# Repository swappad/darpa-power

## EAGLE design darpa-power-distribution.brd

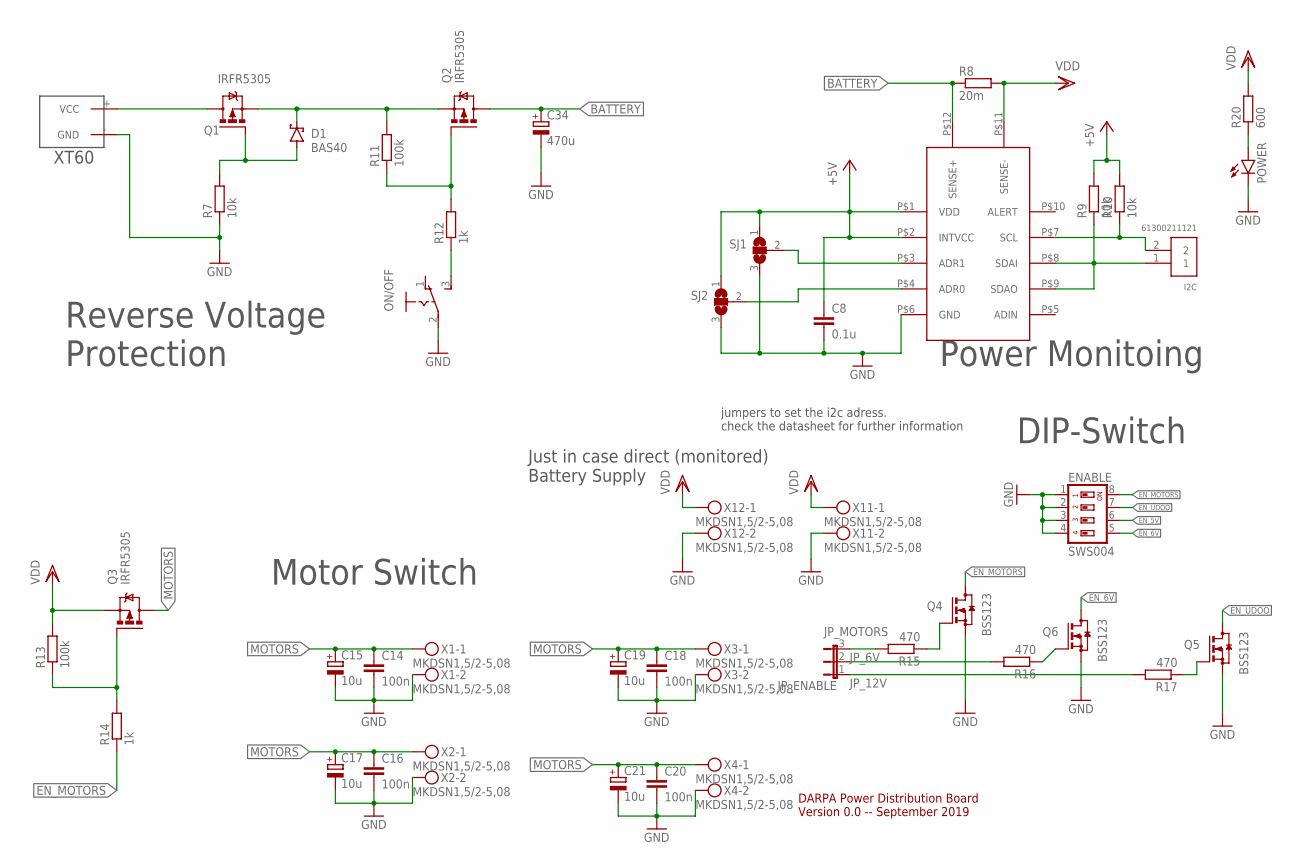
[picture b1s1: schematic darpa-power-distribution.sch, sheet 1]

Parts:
C8: 0.1u; C0805K
C14, C16, C18, C20: 100n; C0805K
C15, C17, C19, C21: 10u; E1,8-4
C34: 470u; E7,5-16
D1: BAS40; SOT23
ENABLE: SWS004; SMS-004
I2C: 61300211121
JP_ENABLE: JP2E; JP2
ON/OFF: M251
POWER: LEDSML0805; SML0805
Q1, Q2, Q3: IRFR5305; D-PAK_TO252AA
Q4, Q5, Q6: BSS123; SOT23
R7, R9, R10: 10k; R0805
R8: 20m; P0613/15
R11, R13: 100k; R0805
R12, R14: 1k; R0805
R15, R16, R17: 470; R0805
R20: 600; R0805
SJ1, SJ2: SJ2W; SJ_2
U$3: LTC2945
U$4: XT60
X1, X2, X3, X4, X11, X12: MKDSN1,5/2-5,08

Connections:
+5V: C8.1, R9.2, R10.2, SJ1.1, SJ2.1, U$3.P$1 (VDD), U$3.P$2 (INTVCC); also elsewhere on the board
BATTERY: C34.+, Q2.4 (D), R8.1, U$3.P$12 (SENSE+)
EN_5V: ENABLE.6; also elsewhere on the board
EN_6V: ENABLE.5, Q6.3 (D); also elsewhere on the board
EN_MOTORS: ENABLE.8, Q4.3 (D), R14.1
EN_UDOO: ENABLE.7, Q5.3 (D); also elsewhere on the board
GND: C8.2, C14.2, C15.-, C16.2, C17.-, C18.2, C19.-, C20.2, C21.-, C34.-, ENABLE.1, ENABLE.2, ENABLE.3, ENABLE.4, ON/OFF.2, POWER.C, Q4.2 (S), Q5.2 (S), Q6.2 (S), R7.1, SJ1.3, SJ2.3, U$3.P$6 (GND), U$4.- (GND), X1.2, X2.2, X3.2, X4.2, X11.2, X12.2; also elsewhere on the board
JP_6V: JP_ENABLE.2, R16.2
JP_12V: JP_ENABLE.1, R17.2
JP_MOTORS: JP_ENABLE.3, R15.2
MOTORS: C14.1, C15.+, C16.1, C17.+, C18.1, C19.+, C20.1, C21.+, Q3.4 (D), X1.1, X2.1, X3.1, X4.1
unnamed: D1.1 (A), Q1.1 (G), R7.2
unnamed: SJ1.2, U$3.P$3 (ADR1)
unnamed: SJ2.2, U$3.P$4 (ADR0)
unnamed: Q2.1 (G), R11.1, R12.2
unnamed: D1.3 (C), Q1.3 (S), Q2.3 (S), R11.2
unnamed: Q3.1 (G), R13.1, R14.2
unnamed: ON/OFF.3 (S), R12.1
unnamed: Q1.4 (D), U$4.+ (VCC)
unnamed: Q5.1 (G), R17.1
unnamed: Q4.1 (G), R15.1
unnamed: Q6.1 (G), R16.1
unnamed: POWER.A, R20.1
SCL: I2C.2, R10.1, U$3.P$7 (SCL)
SDA: I2C.1, R9.1, U$3.P$8 (SDAI), U$3.P$9 (SDAO)
VDD: Q3.3 (S), R8.2, R13.2, R20.2, U$3.P$11 (SENSE-), X11.1, X12.1; also elsewhere on the board

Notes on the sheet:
jumpers to set the i2c adress. check the datasheet for further information
Reverse Voltage Protection
Motor Switch
Power Monitoing
DIP-Switch
Just in case direct (monitored) Battery Supply
DARPA Power Distribution Board Version 0.0 -- September 2019

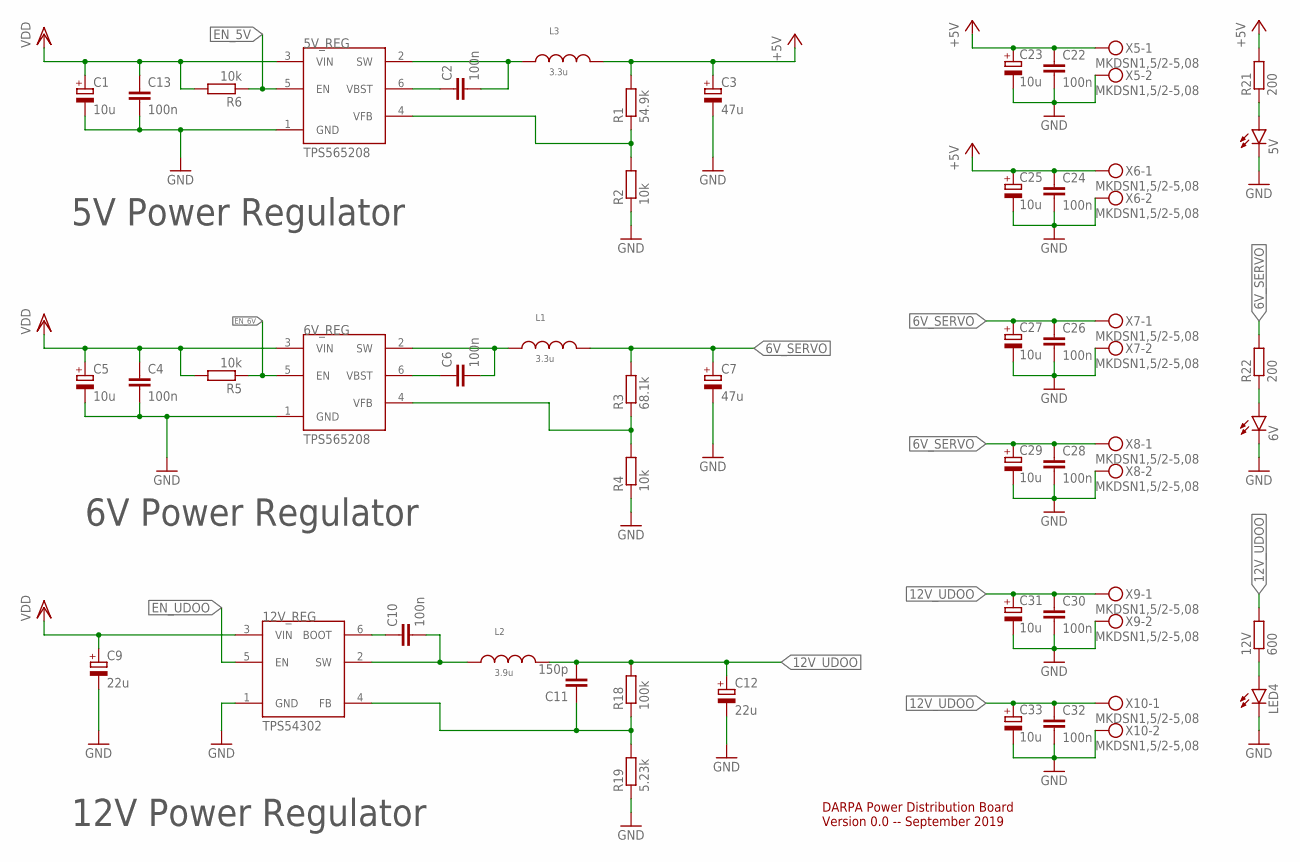
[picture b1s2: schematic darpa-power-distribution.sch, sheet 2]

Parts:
5V, 6V: LEDSML0805; SML0805
5V_REG, 6V_REG: TPS565208; SOT23-6
12V: 600; R0805
12V_REG: TPS54302; SOT23-6
C1, C5, C23, C25, C27, C29, C31, C33: 10u; E1,8-4
C2, C4, C6, C10, C13, C22, C24, C26, C28, C30, C32: 100n; C0805K
C3, C7: 47u; E2,5-6
C9, C12: 22u; E2,5-6
C11: 150p; C0805K
L1, L3: 3.3u; WE-CHSA_1011
L2: 3.9u; WE-CHSA_1011
LED4: LEDSML0805; SML0805
R1: 54.9k; R0805
R2, R4, R5, R6: 10k; R0805
R3: 68.1k; R0805
R18: 100k; R0805
R19: 5.23k; R0805
R21, R22: 200; R0805
X5, X6, X7, X8, X9, X10: MKDSN1,5/2-5,08

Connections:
6V_SERVO: C7.+, C26.1, C27.+, C28.1, C29.+, L1.2, R3.2, R22.2, X7.1, X8.1
12V_UDOO: 12V.2, C11.2, C12.+, C30.1, C31.+, C32.1, C33.+, L2.2, R18.2, X9.1, X10.1
+5V: C3.+, C22.1, C23.+, C24.1, C25.+, L3.2, R1.2, R21.2, X5.1, X6.1; also elsewhere on the board
EN_5V: 5V_REG.5 (EN), R6.1; also elsewhere on the board
EN_6V: 6V_REG.5 (EN), R5.1; also elsewhere on the board
EN_UDOO: 12V_REG.5 (EN); also elsewhere on the board
GND: 5V.C, 5V_REG.1 (GND), 6V.C, 6V_REG.1 (GND), 12V_REG.1 (GND), C1.-, C3.-, C4.2, C5.-, C7.-, C9.-, C12.-, C13.2, C22.2, C23.-, C24.2, C25.-, C26.2, C27.-, C28.2, C29.-, C30.2, C31.-, C32.2, C33.-, LED4.C, R2.1, R4.1, R19.1, X5.2, X6.2, X7.2, X8.2, X9.2, X10.2; also elsewhere on the board
unnamed: 5V_REG.4 (VFB), R1.1, R2.2
unnamed: 5V_REG.6 (VBST), C2.1
unnamed: 5V_REG.2 (SW), C2.2, L3.1
unnamed: 6V_REG.2 (SW), C6.2, L1.1
unnamed: 6V_REG.6 (VBST), C6.1
unnamed: 6V_REG.4 (VFB), R3.1, R4.2
unnamed: 12V_REG.6 (BOOT), C10.1
unnamed: 12V_REG.2 (SW), C10.2, L2.1
unnamed: 12V_REG.4 (FB), C11.1, R18.1, R19.2
unnamed: 5V.A, R21.1
unnamed: 6V.A, R22.1
unnamed: 12V.1, LED4.A
VDD: 5V_REG.3 (VIN), 6V_REG.3 (VIN), 12V_REG.3 (VIN), C1.+, C4.1, C5.+, C9.+, C13.1, R5.2, R6.2; also elsewhere on the board

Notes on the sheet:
5V Power Regulator
6V Power Regulator
12V Power Regulator
DARPA Power Distribution Board Version 0.0 -- September 2019

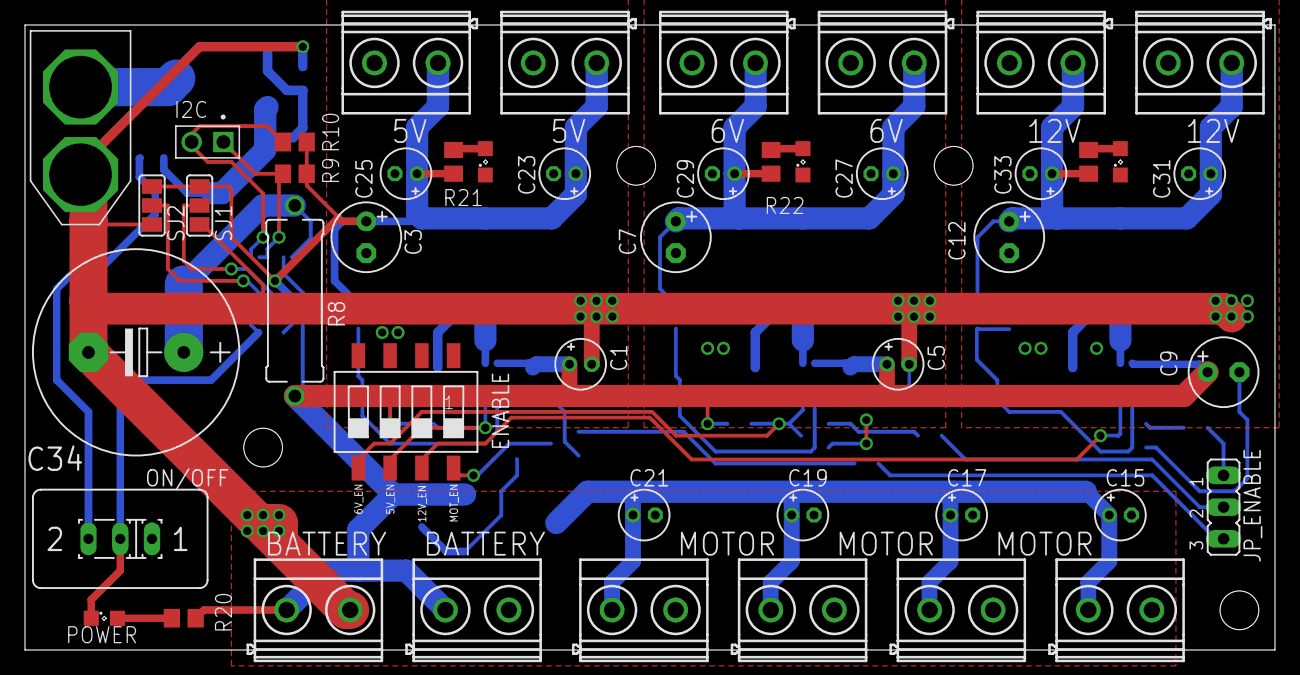
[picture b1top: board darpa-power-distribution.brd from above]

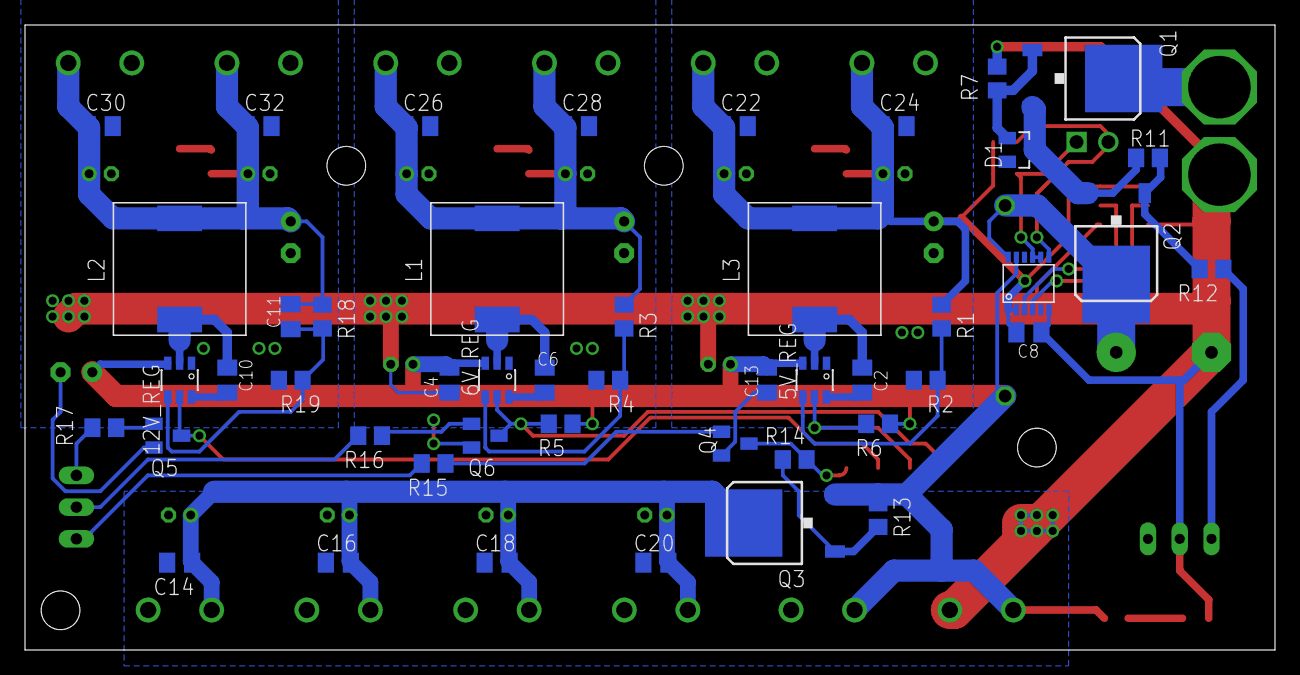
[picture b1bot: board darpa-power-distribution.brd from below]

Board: 2 copper layers, 100.0 x 50.0 mm, 94 parts (47 on the bottom side), 40 nets.

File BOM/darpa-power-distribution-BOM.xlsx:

Qty | Value | Device | Package | Parts | Description | POPULARITY
1 |  | JP2E | JP2 | JP1 | JUMPER | 34
4 |  | LEDSML0805 | SML0805 | LED1, LED2, LED3, LED4 | LED
1 |  | M251 | M251 | S2 | SLIDING SWITCH
2 |  | SJ2W | SJ_2 | SJ1, SJ2 | SMD solder JUMPER
1 | 0.1u | C-EUC0805K | C0805K | C8 | CAPACITOR, European symbol | 52
3 | 100k | R-EU_R0805 | R0805 | R11, R13, R18 | RESISTOR, European symbol | 86
15 | 100n | C-EUC0805K | C0805K | C2, C4, C6, C10, C13, C14, C16, C18, C20, C22, C24, C26, C28, C30, C32 | CAPACITOR, European symbol | 52
7 | 10k | R-EU_R0805 | R0805 | R2, R4, R5, R6, R7, R9, R10 | RESISTOR, European symbol | 86
12 | 10u | CPOL-EUE1.8-4 | E1,8-4 | C1, C5, C15, C17, C19, C21, C23, C25, C27, C29, C31, C33 | POLARIZED CAPACITOR, European symbol | 12
1 | 150p | C-EUC0805K | C0805K | C11 | CAPACITOR, European symbol | 52
2 | 1k | R-EU_R0805 | R0805 | R12, R14 | RESISTOR, European symbol | 86
2 | 200 | R-EU_R0805 | R0805 | R21, R22 | RESISTOR, European symbol | 86
1 | 20m | R-EU_0613/15 | P0613/15 | R8 | RESISTOR, European symbol | 0
2 | 22u | CPOL-EUE2.5-6 | E2,5-6 | C9, C12 | POLARIZED CAPACITOR, European symbol | 26
2 | 3.3u | WE-CHSA_1011_7843330330 | WE-CHSA_1011 | L1, L3 | WE-CHSA SMD High Current Inductor 7843330330/3,3uH
1 | 3.9u | WE-CHSA_1011_7843330330 | WE-CHSA_1011 | L2 | WE-CHSA SMD High Current Inductor 7843330330/3,3uH
3 | 470 | R-EU_R0805 | R0805 | R15, R16, R17 | RESISTOR, European symbol | 86
1 | 470u | CPOL-EUE7.5-16 | E7,5-16 | C34 | POLARIZED CAPACITOR, European symbol | 4
2 | 47u | CPOL-EUE2.5-6 | E2,5-6 | C3, C7 | POLARIZED CAPACITOR, European symbol | 26
1 | 5.23k | R-EU_R0805 | R0805 | R19 | RESISTOR, European symbol | 86
1 | 54.9k | R-EU_R0805 | R0805 | R1 | RESISTOR, European symbol | 86
2 | 600 | R-EU_R0805 | R0805 | R20, R23 | RESISTOR, European symbol | 86
1 | 61300211121 | 61300211121 | 61300211121 | J1 | CONN HEADER VERT 2POS 2.54MM
1 | 68.1k | R-EU_R0805 | R0805 | R3 | RESISTOR, European symbol | 86
1 | BAS40 | BAS40 | SOT23 | D1 | Silicon Schottky Diodes
3 | BSS123 | BSS123 | SOT23 | Q4, Q5, Q6 | N-CHANNEL MOS FET
3 | IRFR5305 | IRFR5305 | D-PAK_TO252AA | Q1, Q2, Q3 | HEXFET Power MOSFET | 4
1 | LTC2945 | LTC2945 | LTC2945 | U$3
12 | MKDSN1,5/2-5,08 | MKDSN1,5/2-5,08 | MKDSN1,5/2-5,08 | X1, X2, X3, X4, X5, X6, X7, X8, X9, X10, X11, X12 | MKDSN 1,5/ 2-5,08 Printklemme
1 | SWS004 | SWS004 | SMS-004 | S1 | SMD Dip Switch 4 pol.
1 | TPS54302 | TPS54302 | SOT23-6 | U$5
2 | TPS565208 | TPS565208 | SOT23-6 | U$1, U$2
1 | XT60 | XT60 | XT60 | U$4 | XT60

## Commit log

2019-09-05 placing improved. routing proceeded
2019-09-07 proceeded routing. changes in positioning
2019-09-09 proceed routing
2019-09-09 routing completed; Errors fixed; added LEDs and BOM; TODO: DRC, second cheack and approval
2019-09-15 corrected typo in resistor value
2019-09-17 placing improved, DRC done, labels aligned
2019-09-17 little changes
2019-10-29 BOM updated for the next order
2019-12-03 schematics and layout added as pdf
2020-01-10 contours added as .dxf

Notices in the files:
parts and their libraries:
Wurth_Elektronik_Passive_rev19e: Copyright: Würth Elektronik
